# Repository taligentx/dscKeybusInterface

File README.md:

# DSC Keybus Interface

This library directly interfaces Arduino, esp8266, and esp32 series microcontrollers to [DSC PowerSeries](http://www.dsc.com/dsc-security-products/g/PowerSeries/4) and [Classic series](https://www.dsc.com/manual/29000203) security systems for integration with home automation, remote control as a virtual keypad, notifications on alarm events, unlocking installer codes, and emulating DSC panels to use DSC keypads as general purpose input devices.

This enables existing DSC security system installations to retain the features and reliability of a hardwired system while integrating with modern devices and software for under $5USD in components.

The built-in examples can be used as-is or as a base to adapt to other uses:
* Home automation integration: [Home Assistant](https://www.home-assistant.io), [Apple HomeKit & Siri](https://www.apple.com/ios/home/), [Google Home](https://assistant.google.com), [OpenHAB](https://www.openhab.org), [Athom Homey](https://www.athom.com/en/)
* Remote control: Web interface, [Blynk](https://www.blynk.io) mobile app, [Telegram](https://www.telegram.org) bot (with remote arming/disarming via chat)
* Notifications: [Pushover](https://www.pushover.net), [PushBullet](https://www.pushbullet.com), [Pushsafer](https://www.pushsafer.com), [Twilio SMS](https://www.twilio.com), [TinyGSM SMS](https://github.com/vshymanskyy/TinyGSM), E-mail
* Keypad interface: Emulates a DSC panel to connect DSC keypads as physical input devices for any general purpose, without a DSC panel.
* Installer code unlocking: Automatic code search to unlock panels with unknown installer codes

Example integrations:
* [Apple Home & Siri](https://www.apple.com/ios/home/):  
  
* [Home Assistant](https://www.home-assistant.io):  
  
* [OpenHAB](https://www.openhab.org) MQTT:  
  
* [Blynk](https://www.blynk.io) app virtual keypad:
  
* Web virtual keypad:  
  
* [Telegram](https://www.telegram.org) bot:  

## Quick start
1. Install the DSC Keybus Interface library:
    * Arduino IDE: Search for `DSC` in the Library Manager - `Sketch > Include Library > Manage Libraries`  
      
    * PlatformIO IDE: Search for `DSC` in the [PlatformIO Library Registry](https://platformio.org/lib/show/5499/dscKeybusInterface)  
      
    * PlatformIO CLI: `platformio lib install "dscKeybusInterface"`
    * Alternatively, `git clone` or download the repo .zip to the Arduino/PlatformIO library directory to keep track of the latest changes.
2. Select, configure, and upload one of the example sketches to the microcontroller:  
      
3. Connect the microcontroller to the DSC Keybus per the wiring diagram with the appropriate resistors (and a transistor if you'd like to control the system).

## Why?
**I Had**: _A DSC security system not being monitored by a third-party service._  
**I Wanted**: _Notification if the alarm triggered._

I was interested in finding a solution that directly accessed the pair of data lines that DSC uses for their proprietary Keybus protocol to send data between the panel, keypads, and other modules (instead of using the DSC IT-100 serial module).  Tapping into the data lines is an ideal task for a microcontroller and also presented an opportunity to work with the [Arduino](https://www.arduino.cc) and [FreeRTOS](https://www.freertos.org) (via [esp-open-rtos](https://github.com/SuperHouse/esp-open-rtos)) platforms.

While there has been excellent [discussion about the DSC Keybus protocol](https://www.avrfreaks.net/s/topic/a5C3l000000ULgIEAW/t097136) and several existing projects, there were a few issues that remained unsolved:
* Error-prone Keybus data capture.
* Limited data decoding - there was good progress for armed/disarmed states and partial zone status for a single partition, but otherwise most of the data was undecoded (notably missing the alarm triggered state).
* Read-only - unable to control the Keybus to act as a virtual keypad.
* No implementations to do useful work with the data.

This library uses a combination of hardware and timer interrupts to accurately capture Keybus data, and has lead to reverse engineering much of the Keybus protocol.

## Features
* Monitor the status of all partitions:
  - Alarm triggered, armed/disarmed, entry/exit delay, fire triggered, keypad panic keys
* Monitor zones status:
  - Zones open/closed, zones in alarm
* Monitor system status:
  - Ready, trouble, AC power, battery
* Monitor PGM outputs 1-14 status
* Virtual keypad:
  - Write keys to the panel for all partitions
  - Trigger panel command outputs
* Keypad interface:
  - Emulates a DSC panel to use DSC PowerSeries and Classic series keypads as physical input devices for any general purpose, without needing a DSC panel.
* Panel time - retrieve current panel date/time and set a new date/time (including an example with NTP sync)
* Panel installer code unlocking - determine the 4-digit panel installer code
* Virtual zone expander - the [expander branch](https://github.com/taligentx/dscKeybusInterface/tree/expander) can emulate a DSC zone expander module to add zones to the security system that are handled by the microcontroller - thanks to [Dilbert66](https://github.com/Dilbert66) for this contribution!
* Direct Keybus interface:
  - Does not require the [DSC IT-100 serial interface](https://www.dsc.com/alarm-security-products/IT-100%20-%20PowerSeries%20Integration%20Module/22).
* Designed for reliable data decoding and performance:
  - Hardware GPIO pin interrupts and timer interrupts for accurate data capture timing
  - Data buffering: helps prevent lost Keybus data if the sketch is busy
  - Extensive data decoding: the majority of Keybus data as seen in the [DSC IT-100 Data Interface developer's guide](https://cms.dsc.com/download.php?t=1&id=16238) has been reverse engineered and documented in [`src/dscKeybusPrintData.cpp`](https://github.com/taligentx/dscKeybusInterface/blob/master/src/dscKeybusPrintData.cpp).
  - Non-blocking code: Allows sketches to run as quickly as possible without using `delay` or `delayMicroseconds`
* Supported security systems:
  - [DSC PowerSeries](https://www.dsc.com/?n=enduser&o=identify) - all panels are supported, tested with: PC585, PC1555MX, PC1565, PC1565-2P, PC5005, PC5010, PC5015, PC5020, PC1616, PC1808, PC1832, PC1864
  - [DSC Classic series](https://www.dsc.com/?n=enduser&o=identify): PC1500, PC1550, PC2550
    * Requires configuring the panel through `*8` programming to enable PC16-OUT mode - see [DSC Configuration](https://github.com/taligentx/dscKeybusInterface/tree/master?tab=readme-ov-file#dsc-configuration)
    * PC2500 and PC3000 require testing, [post an issue](https://github.com/taligentx/dscKeybusInterface/issues) if you're able to test these panels.
  - Rebranded DSC PowerSeries (such as some ADT systems) should also work with this interface.
* Unsupported security systems:
  - DSC Alexor (PC9155) is all wireless and does not have an accessible Keybus interface.
  - DSC Neo series use a higher speed encrypted data protocol (Corbus) that is not currently possible to support.
  - Other brands (that are not rebranded DSC systems) use different protocols and are not supported.
    * For Honeywell Ademco Vista 15P/20P, see [Dilbert66's esphome-vistaECP](https://github.com/Dilbert66/esphome-vistaECP) project
    * For Paradox systems, see [liaan's paradox-esp8266](https://github.com/liaan/paradox_esp8266) project
* Supported microcontrollers:
    - [Arduino](https://www.arduino.cc/en/Main/Products):
      * Boards: Uno, Mega, Leonardo, Mini, Micro, Nano, Pro, Pro Mini
      * ATmega328P, ATmega2560, and ATmega32U4-based boards at 16Mhz
    - esp8266:
      * Development boards: NodeMCU v2 or v3, Wemos D1 Mini, etc.
      * Includes [Arduino framework support](https://github.com/esp8266/Arduino) and WiFi for ~$3USD shipped.
    - esp32, esp32-s2, esp32-s3, esp32-c3:
      * Includes [Arduino framework support](https://github.com/espressif/arduino-esp32) (v2.0.2 or newer required) for $3-5USD shipped.
* Possible features (PRs welcome!):
  - [DSC IT-100](https://cms.dsc.com/download.php?t=1&id=16238) emulation
  - Unlock 6-digit installer codes

## Release notes
* develop
  - New: Keybus decoding for module programming, PC5200, and zones 33-64 extended status - thanks to [kricon](https://github.com/kricon) for this contribution!
  - New: Classic series PC3000 support (experimental) - with considerations from the PC3000 code by [sfossen](https://github.com/sfossen). The implementations differ, you can also test his original code which is now preserved in the [pc3000 branch](https://github.com/taligentx/dscKeybusInterface/tree/pc3000).
  - New: Isolated `KeybusReader`-specific library functions to capture module data and print Keybus data, reduces size and memory usage across all sketches
  - Updated: `Unlocker` sketch support for DSC Classic series
  - Updated: `HomeAssistant-MQTT` example configuration for Home Assistant core 2022.06, support changing armed modes while armed, add fire/aux/panic buttons
  - Updated: `VirtualKeypad-Web` to support ArduinoJSON 7.x, use LittleFS for esp8266
* 3.0
  - New: DSC Classic series panel support: PC1500, PC1550, PC2550 - thanks to [kricon](https://github.com/kricon) for extensively testing and contributing to this!
  - New: `KeypadInterface` and `KeypadInterface-MQTT` example sketches - emulate a DSC panel to connect DSC PowerSeries and Classic keypads as physical input devices for any general purpose, without needing a DSC panel.
  - New: `HomeKit-HomeSpan` example sketch (esp32) - integrate directly with Apple HomeKit as a native standalone accessory using [HomeSpan](https://github.com/HomeSpan/HomeSpan)
  - New: [Pushover](https://www.pushover.net) and [Pushsafer](https://www.pushsafer.com) push notification example sketches for esp8266/esp32
  - New: esp32-s2 microcontroller support
  - New: Code restructured to support new features from sketches using #define flags - enables Classic series support and `KeypadInterface`.
  - Updated: `Homebridge-MQTT` supports switching armed modes while armed
  - Updated: Added TLS root certificate to `Twilio-SMS`
  - Updated: removed deprecated `handlePanel()`
  - Bugfix: `VirtualKeypad-Web` updated notes to switch to [this fork of ESPAsyncWebServer](https://github.com/arjenhiemstra/ESPAsyncWebServer) to resolve crashes with iOS and macOS clients.
  - Bugfix: `Pushbullet` example sketch updated TLS security certificate fingerprint
  - Bugfix: Workaround for [upstream esp32 TLS handshake issue](https://github.com/espressif/arduino-esp32/issues/6165) preventing making a TLS connection more than once.
  - Bugfix: Fixed `Homebridge-MQTT` handling exit delay states while multiple partitions are arming
  - Bugfix: Resolved access codes not updating on disarm, changed arming access codes to update before armed status changes
* 2.0
  - New: [Telegram](https://www.telegram.org) bot example sketch
  - New: [OpenHAB](https://www.openhab.org) integration example sketch using MQTT
  - New: `Unlocker` example sketch - determines the panel installer code
  - New: `TimeSyncNTP` example sketch - uses NTP to automatically set the panel time
  - New: [ESPHome](https://esphome.io) integration example (located in the `extras` directory) - thanks to [Dilbert66](https://github.com/Dilbert66) for this contribution!
  - New: `TinyGSM-SMS` example sketch - sends status via SMS with a GSM modem - thanks to [jvitkauskas](https://github.com/jvitkauskas) for this contribution!
  - New: `KeybusReaderIP` example sketch enables Keybus data access over IP, thanks to [aboulfad](https://github.com/aboulfad) for this contribution!
  - New: esp32 microcontroller support - requires [Arduino-esp32](https://github.com/espressif/arduino-esp32) v1.0.5-rc6 or newer
  - New: Features for sketches:
      * `ready` and `disabled` track partition status
      * `setTime()` sets the panel date and time
      * `pgmOutputs[]` tracks the status of PGM outputs 1-14
      * `timestampChanged` tracks when the panel sends a timestamp
      * `accessCode` tracks the access code used to arm/disarm
      * `resetStatus()` triggers a full status update of all partitions and zones - for example, after initialization or a lost network connection.
      * `pauseStatus` pauses status updates if set to `true` - for example, holding status changes during a lost network connection
      * `stop()` disables the interface - for example, prior to starting OTA updates
      * `appendPartition()` in example sketches simplifies adding partition numbers to messages
      * `panelVersion` tracks the panel version number
  - New: Handle `*1 bypass/re-activate` used to change stay/away mode while armed
  - Updated: `VirtualKeypad-Blynk` and `VirtualKeypad-Web` display alarm memory, programming zone lights, and event buffer
  - Updated: `HomeAssistant-MQTT, Homebridge-MQTT, OpenHAB-MQTT` include PGM outputs 1-14 status
  - Updated: Virtual keypad writes
      * `write()` for multiple keys can now be set to block until the write is complete with an optional parameter if the char array is ephemeral
      * Checking `writeReady` is typically no longer needed in the sketch, the library will block if a previous write is in progress - this can be checked if the sketch needs to wait until the library can perform a nonblocking write
  - Updated: `HomeAssistant-MQTT` sketch now includes night arm and for esp8266/esp32 includes a sensor with partition status messages
  - Updated: Expanded partition state processing to improve panel state detection at startup
  - Deprecated: `handlePanel()` is now `loop()`
  - Bugfix: Resolved keypad aux/panic key, AC power, and battery status on PC585/PC1555MX
  - Bugfix: Resolved `Homebridge-MQTT` sketch not handling HomeKit target states
  - Bugfix: Resolved timing issues when consecutively calling `write`
* 1.2
  - New: Virtual keypad web interface example, thanks to [Elektrik1](https://github.com/Elektrik1) for this contribution!
    - As of esp8266 Arduino Core 2.5.1, you may need to [manually update the esp8266FS plugin](https://github.com/esp8266/arduino-esp8266fs-plugin) for SPIFFS upload.
  - New: Support esp8266 CPU running at 160MHz - this helps sketches using TLS through BearSSL
  - Updated: HomeAssistant-MQTT example includes availability status, thanks to [bjrolfe](https://github.com/bjrolfe) for this contribution!
  - Updated: List of tested DSC panels: PC585, PC1565, PC5005, PC1808
  - Updated: esp8266 power wiring diagrams
  - Updated: esp8266 module list
* 1.1
  - New: Zones 33-64 tamper and fault decoding
  - New: Push notification example using [Twilio](https://www.twilio.com), thanks to [ColingNG](https://github.com/ColinNg) for this contribution!
  - Bugfix: Zones 17-32 status incorrectly stored
* 1.0
  - New: [Blynk](https://www.blynk.io) virtual keypad example sketch and app layout examples
  - New: Virtual keypad support for PGM terminals 1-4 command output
  - New: Status `keybusConnected` to check if data is being received from the DSC panel
  - New: Auxiliary input alarm decoding
* 0.4
  - New: Virtual keypad support for partitions 3-8, thanks to [jvitkauskas](https://github.com/jvitkauskas) for contributing the necessary logs
  - New: Support ATmega32U4-based Arduino boards (switched to AVR Timer1)
  - Changed: Simplified example names, configurations, added version numbers
  - Bugfix: Virtual keypad writes with partitions 5-8 enabled
  - Bugfix: F/A/P alarm key writes with `processModuleData` disabled
  - Bugfix: HomeAssistant example `configuration.yaml` error for `alarm_control_panel`
* 0.3
  - New: Status for partitions 2-8, zones 33-64
  - New: Virtual keypad support for partition 2
  - New: [Athom Homey](https://www.athom.com/en/) integration example sketch, thanks to [MagnusPer](https://github.com/MagnusPer) for this contribution!
  - New: PCB layouts, contributed by [sjlouw](https://github.com/sj-louw)
  - New: Configurable number of partitions and zones to customize memory usage: `dscPartitions` and `dscZones` in `dscKeybusInterface.h`
  - New: KeybusReader decoding of commands `0xE6` and `0xEB`
  - Changed: Split examples by platform
  - Changed: Arduino sketches no longer use pin 4 to avoid a conflict with the SD card on Ethernet shields.
  - Changed: MQTT examples updated with username and password fields
  - Changed: `processRedundantData` now true by default to prevent storing repetitive data, reduces memory usage.
  - Note: This release changes the library methods to accommodate multiple partitions, existing sketches will need to be updated to match the new example sketches.
* 0.2
  - New: Status for zones 9-32
  - New: [Home Assistant](https://www.home-assistant.io) integration example sketch
  - New: Panel data buffering, adds `dscBufferSize` to `dscKeybusInterface.h` to allow configuration of how many panel commands are buffered to customize memory usage (uses 18 bytes of memory per command buffered).
* 0.1 - Initial release

## Examples
The included examples demonstrate how to use the library and can be used as-is or adapted to integrate with other software.  Post an issue/pull request if you've developed (and would like to share) a sketch/integration that others can use.

* **Status**: Processes and prints the security system status to a serial interface, including reading from serial for the virtual keypad.  This demonstrates how to determine if the security system status has changed, what has changed, and how to take action based on those changes.  Post an issue/pull request if you have a use for additional system states - for now, only a subset of all decoded commands are being tracked for status to limit memory usage:
  * Partitions ready
  * Partitions armed away/stay/disarmed
  * Partitions in alarm
  * Partitions exit delay in progress
  * Partitions entry delay in progress
  * Partitions fire alarm
  * Zones open/closed
  * Zones in alarm
  * PGM outputs 1-14
  * Keypad fire/auxiliary/panic alarm
  * Get/set panel date and time
  * User access code number (1-40)
  * Panel AC power
  * Panel battery
  * Panel trouble
  * Keybus connected

* **HomeKit-HomeSpan** (esp32): Integrates directly with Apple HomeKit as a native accessory (for the Home app and Siri) using [HomeSpan](https://github.com/HomeSpan/HomeSpan), without needing a separate service or device.  Demonstrates arming/disarming partitions, zones status, fire alarms, PGM outputs status, and controlling panel command outputs.
    - For esp8266, the [dscKeybusInterface-RTOS](https://github.com/taligentx/dscKeybusInterface-RTOS) library includes a native HomeKit implementation that runs directly on the esp8266, without requiring a separate device running MQTT or Homebridge.

* **Homebridge-MQTT**: Interfaces with [Homebridge](https://github.com/nfarina/homebridge) via MQTT to integrate with Apple HomeKit (including the iOS Home app and Siri) and [Google Home](https://github.com/oznu/homebridge-gsh).  Demonstrates arming/disarming partitions and for HomeKit, viewing the status of zones, PGM outputs, and fire alarms.

* **HomeAssistant-MQTT**: Interfaces with [Home Assistant](https://www.home-assistant.io) via MQTT.  Demonstrates arming/disarming partitions and viewing the status of zones, PGM outputs, fire alarms, and trouble.  For esp8266/esp32, the partition status is available as a text message for display.

* **OpenHAB-MQTT**: Interfaces with [OpenHAB](https://www.openhab.org) via MQTT.  Demonstrates using the panel and partitions states as OpenHAB switches and zone states as OpenHAB contacts.  For esp8266/esp32, a panel status message is also sent as a string to OpenHAB.  See https://github.com/jimtng/dscalarm-mqtt for an integration using the Homie convention for OpenHAB's Homie MQTT component.

* **ESPHome** (esp8266): Integrates with [ESPHome](https://esphome.io) as a custom component - note that this example is located in the `extras` directory.  Thanks to [Dilbert66](https://github.com/Dilbert66) for this contribution!

* **Homey**: Integrates with [Athom Homey](https://www.athom.com/en/) and the [Homeyduino](https://github.com/athombv/homey-arduino-library/) library, including armed, alarm, and fire states (currently limited to one partition), and zone states.  Thanks to [MagnusPer](https://github.com/MagnusPer) for contributing this example!

* **Telegram** (esp8266/esp32):  Demonstrates sending status updates as push notifications and arming/disarming the security system via a [Telegram](https://www.telegram.org) bot.  Supports iOS, Android, and macOS/Windows/Linux desktop notifications (free).

* **Pushover** (esp8266/esp32):  Demonstrates sending status updates as push notifications via [Pushover](https://www.pushover.net).  Supports iOS, Android, macOS native desktop notifications, and Chrome/Firefox/Safari browser popups ($4.99USD one-time purchase per client platform).

* **Pushbullet** (esp8266/esp32):  Demonstrates sending status updates as push notifications via [Pushbullet](https://www.pushbullet.com).  Supports Android, Windows desktop notifications, and Chrome/Firefox browser popups (free).  Note that iOS is no longer supported.

* **Pushsafer** (esp8266/esp32):  Demonstrates sending status updates as push notifications via [Pushsafer](https://www.pushsafer.com).  Supports iOS, Android, Windows desktop notifications, and Chrome/Firefox/Edge/Opera/Yandex browser popups (€0.99EUR or less per 1000 notifications).

* **Twilio-SMS** (esp8266/esp32): Demonstrates sending status updates as SMS text messages via [Twilio](https://www.twilio.com) - thanks to [ColingNG](https://github.com/ColinNg) for contributing this example!

* **Email** (esp8266/esp32): Demonstrates sending status updates as email.  Email is sent using SMTPS (port 465) with SSL for encryption - this is necessary on the esp8266/esp32 until STARTTLS can be supported.  For example, this will work with Gmail after changing the account settings to [allow less secure apps](https://support.google.com/accounts/answer/6010255).

  This can be used to send SMS text messages if the number's service provider has an [email to SMS gateway](https://en.wikipedia.org/wiki/SMS_gateway#Email_clients) - examples for the US:
  * T-mobile: 5558675309@tmomail.net
  * Verizon: 5558675309@vtext.com
  * AT&T: 5558675309@txt.att.net

* **VirtualKeypad-Blynk** (esp8266/esp32): Provides a virtual keypad interface for the free [Blynk legacy](https://www.blynk.io) app on iOS and Android, including viewing alarm memory, programming zone lights, and the event buffer.  The newer generation Blynk app is not currently supported.  Scan one of the following QR codes from within the Blynk app for an example keypad layout:
  - [Virtual keypad with 16 zones](https://user-images.githubusercontent.com/12835671/103719316-5f6f1d80-4f8e-11eb-8a7c-4bd7bfe3cd8a.png)
  - [Virtual keypad with 32 zones](https://user-images.githubusercontent.com/12835671/103719459-af4de480-4f8e-11eb-8e4a-7172961e2d29.png)
  - [Virtual keypad with 8 zones and event log](https://user-images.githubusercontent.com/12835671/103719518-cc82b300-4f8e-11eb-8b2a-97299e7be3a2.png)

  Note: Installing [Blynk as a local server](https://github.com/Peterkn2001/blynk-server) is recommended to keep control of the security system internal to your network.

* **VirtualKeypad-Web** (esp8266/esp32): Provides a virtual keypad web interface, using the esp8266/esp32 itself as a standalone web server, including viewing alarm memory, programming zone lights, and the event buffer.  Thanks to [Elektrik1](https://github.com/Elektrik1) for contributing this example!

* **TimeSyncNTP**:  Synchronizes and maintains time on PowerSeries panels via an NTP server, including DST adjustments.

* **Unlocker**: Finds the 4-digit installer code for PowerSeries panels by checking all possible codes, including handling keypad lockout if enabled.  The valid code is output to serial as well as repeatedly flashed with the built-in LED.  Arduino checks each code sequentially but esp8266/esp32 may find the code more quickly as they check in order of the [most commonly used general 4-digit codes](http://www.datagenetics.com/blog/september32012).

* **KeypadInterface**:  Interfaces directly to DSC PowerSeries and Classic series (tested with PC1500RK) keypads (without a DSC panel) to enable using these as physical inputs for any general purpose.  Examples included for interfacing via serial and MQTT.  Note that this uses a different wiring setup from the standard Keybus interface, refer to the wiring diagram in the example sketch.

* **KeybusReader**: Decodes and prints data from the Keybus to a serial interface, including reading from serial for the virtual keypad.  This can be used to help decode the Keybus protocol and is also handy as a troubleshooting tool to verify that data is displayed without errors.  For esp8266/esp32, `KeybusReaderIP` enables connectivity over WiFi.

  See [`src/dscKeybusPrintData.cpp`](https://github.com/taligentx/dscKeybusInterface/blob/master/src/dscKeybusPrintData.cpp) for all currently known Keybus protocol commands and messages.  Issues and pull requests with additions/corrections are welcome!

## More DSC projects
* **[dscalarm-mqtt](https://github.com/jimtng/dscalarm-mqtt)**: implementation of the [Homie](https://homieiot.github.io) MQTT convention
* **[esphome-dsckeybus](https://github.com/Dilbert66/esphome-dsckeybus)**: implementation of this library as an ESPHome custom component
* **[PC1500KeybusReader](https://github.com/polishedmarvin/dscKeybusInterface)**: MQTT HomeKit example for the PC1500 and ESP32 using [dougkpowers/pc1550-interface](https://github.com/dougkpowers/pc1550-interface)

## Wiring

```
DSC Aux(+) ---+--- Arduino Vin pin
              |
              +--- 5v voltage regulator --- esp8266 NodeMCU / Wemos D1 Mini 5v pin
                                            esp32 development board 5v pin

DSC Aux(-) --- Arduino/esp8266/esp32 Ground

                        Arduino        +--- dscClockPin (Arduino Uno: 3)
DSC Yellow ---+--- 15k ohm resistor ---|
              |                        +--- 10k ohm resistor --- Ground
              |
              |     esp8266/esp32      +--- dscClockPin (esp8266: D1, GPIO 5 / esp32: 18)
              +--- 33k ohm resistor ---|
                                       +--- 10k ohm resistor --- Ground

                        Arduino        +--- dscReadPin (Arduino Uno: 5)
DSC Green ----+--- 15k ohm resistor ---|
              |                        +--- 10k ohm resistor --- Ground
              |
              |     esp8266/esp32      +--- dscReadPin (esp8266: D2, GPIO 4 / esp32: 19)
              +--- 33k ohm resistor ---|
                                       +--- 10k ohm resistor --- Ground

Classic series only, PGM configured for PC16-OUT mode:
DSC PGM ------+--- 1k ohm resistor --- DSC Aux(+)
              |
              |         Arduino        +--- dscPC16Pin (Arduino Uno: 4)
              +--- 15k ohm resistor ---|
              |                        +--- 10k ohm resistor --- Ground
              |
              |     esp8266/esp32      +--- dscPC16Pin (esp8266: D7, GPIO 13 / esp32: 17)
              +--- 33k ohm resistor ---|
                                       +--- 10k ohm resistor --- Ground

Virtual keypad (optional):
DSC Green ---- NPN collector --\
                                |-- NPN base --- 1k ohm resistor --- dscWritePin (Arduino Uno: 6 / esp8266: D8, GPIO 15 / esp32: 21)
      Ground --- NPN emitter --/
```

* The DSC PowerSeries Keybus operates at ~12.6v and the Classic series operates at ~13.75v, a pair of resistors per data line will bring this down to an appropriate voltage for each microcontroller.
    * Arduino:
      * The DSC yellow (clock) line connects to a [hardware interrupt pin](https://www.arduino.cc/reference/en/language/functions/external-interrupts/attachinterrupt/) - for the Uno, these are pins 2 or 3.  The example sketches use dscClockPin: 3.
      * The DSC green (data) line can be connected to any of the remaining digital pins 2-12.  The examples sketches use dscReadPin: 5 and dscWritePin: 6.
    * esp8266: connect the DSC lines to GPIO pins that are normally low to avoid putting spurious data on the Keybus: D1 (GPIO5), D2 (GPIO4) and D8 (GPIO15).  The example sketches use dscClockPin: D1, dscReadPin: D2, dscWritePin: D8.  For the Classic series, dscPC16Pin: D7 (GPIO 13).
    * esp32: connect the DSC lines to GPIO pins that do not send signals at boot: 4, 13, 16-39.  For virtual keypad, use pins 4, 13, 16-33 - pins 34-39 are input only and cannot be used.  The example sketches use dscClockPin: 18, dscReadPin: 19, dscWritePin: 21.  For the Classic series, dscPC16Pin: 17.
* Virtual keypad uses an NPN transistor and a resistor to write to the Keybus.  Most small signal NPN transistors should be suitable, for example:
  * 2N3904
  * BC547, BC548, BC549
  * That random NPN at the bottom of your parts bin (my choice)
* Power:
  * Arduino boards can be powered directly from the DSC panel
  * esp8266/esp32 development boards should use an external voltage regulator set to 5v to the 5v pin:
    - LM2596-based step-down buck converter modules are reasonably efficient and commonly available for under $1USD shipped (eBay, Aliexpress, etc) - these are the modules I use.
    - MP2307-based step-down buck converter modules (aka Mini360) are also available but some versions run hot with an efficiency nearly as poor as linear regulators.
    - Linear voltage regulators (LM7805, etc) will work but are inefficient and run hot - these may need a heatsink.
  * esp8266/esp32 boards can also use an external voltage regulator set to 3.3v to the 3.3v pin - this bypasses the module's onboard voltage regulator.  For example, some Wemos D1 mini clones use [low current voltage regulators](https://www.letscontrolit.com/forum/viewtopic.php?t=6603) that can cause stability issues.  NodeMCU boards are not affected as they use the more powerful AMS1117 regulator.
* Connections should be soldered, breadboards can cause issues.

## Virtual keypad
This allows a sketch to send keys to the DSC panel to emulate the physical DSC keypads and enables full control of the panel from the sketch or other software.

Keys are sent to partition 1 by default and can be changed to a different partition.  The following keys can be sent to the panel - see the examples for usage:

* Keypad: `0-9 * #`
* Arm stay (requires access code if quick arm is disabled): `s`
* Arm away (requires access code if quick arm is disabled): `w`
* Arm with no entry delay (requires access code): `n`
* Fire alarm: `f`
* Auxiliary alarm: `a`
* Panic alarm: `p`
* Door chime enable/disable: `c`
* Fire reset: `r`
* Quick exit: `x`
* Change partition: `/` + `partition number` or set `writePartition` to the partition number.  Examples:
  * Switch to partition 2 and send keys: `/2` + `1234`
  * Switch back to partition 1: `/1`
  * Set directly in sketch: `dsc.writePartition = 8;`
* Command output 1: `[`
* Command output 2: `]`
* Command output 3: `{`
* Command output 4: `}`

## DSC Configuration
Panel options affecting this interface, configured by `*8 + installer code` - see the `Unlocker` sketch if your panel's installer code is unknown.  Refer to the DSC installation manual for your panel to configure these options:
* Swinger shutdown: By default, the panel will limit the number of alarm commands sent in a single armed cycle to 3 - for example, a zone alarm being triggered multiple times will stop reporting after 3 alerts.  This is to avoid sending alerts repeatedly to a third-party monitoring service, and also affects this interface.  As I do not use a monitoring service, I disable swinger shutdown by setting this to `000`.
  - PC1555MX/5015: section `370`
  - PC1616/PC1832/PC1864 section `377`
  - PC1500/PC1550: section `15`
  - PC2550: section `22`

* AC power failure reporting delay: The default delay is 30 minutes and can be set to `000` to immediately report a power failure.
  - PC1555MX/5015: section `370`
  - PC1616/PC1832/PC1864 section `377`
  - PC1500/PC1550: section `17`
  - PC2500: section `16`
  - PC2550: section `20`
  - PC3000: section `22`

* Classic series - requires PC16-OUT mode to get the security system status (see wiring section):
  - Communicator: Enable to support PC16-OUT mode (if not using a monitoring service, "Communicator Call Directions" options can be set to `0`)
    - PC1500/PC1550: section `12`, option `1` off
    - PC2500: section `13`, option `1` off
    - PC2550: section `15`, option `1` off
    - PC3000: section `18`, option `1` off
  - PC16-OUT: Enable to set the PGM output to PC16-OUT mode to send required panel status data on the Keybus.
    - PC1500/PC1550: section `13`, option `4` on
    - PC2500: section `14`, option `4` on
    - PC2550: section `16`, option `4` on
    - PC3000: section `19`, option `4` on
  - PGM output: Set to "Strobe output" mode to track when the alarm is tripped.
    - PC1500/PC1550: section `24`, option `08`
    - PC2500: section `22`, option `x8` (first digit is aux input zone configuration, default `2`)
    - PC2550: section `30`, option `x8`
    - PC3000: section `28`, option `x8`

## Notes
* For OTA updates on esp8266 and esp32, you may need to stop the interface using `dsc.stop();`:
  ```
  void setup() {
    ...
    ArduinoOTA.onStart( {
      dsc.stop();
    ...
  ```
* Memory usage can be adjusted based on the number of partitions, zones, and data buffer size specified in [`src/dscKeybus.h`](https://github.com/taligentx/dscKeybusInterface/blob/master/src/dscKeybus.h) or [`src/dscClassic.h`](https://github.com/taligentx/dscKeybusInterface/blob/master/src/dscClassic.h).   Default settings:
  * Arduino: up to 4 partitions, 32 zones, 10 buffered commands
  * esp8266/esp32: up to 8 partitions, 64 zones, 50 buffered commands

* PCB layouts are available in [`extras/PCB Layouts`](https://github.com/taligentx/dscKeybusInterface/tree/master/extras/PCB%20Layouts) - thanks to [sjlouw](https://github.com/sj-louw) for contributing these designs!

* Support for other platforms depends on adjusting the code to use their platform-specific timers.  In addition to hardware pin-change interrupts to capture the DSC clock, this library uses platform-specific timer interrupts to capture the DSC data line in a non-blocking way 250μs after the clock changes (without using `delayMicroseconds()`).  This is necessary because the clock and data are asynchronous - I've observed keypad data delayed up to 160μs after the clock falls.

* Resource utilization:
  * Arduino: 1 hardware interrupt digital pin, 2 digital pins (+1 for Classic series), Timer1 interrupt
  * esp8266: 3 digital pins (+1 for Classic series), timer1 interrupt
  * esp32 series: 3 digital pins (+1 for Classic series), timer0 interrupt

## Troubleshooting
If you are running into issues:
1. Run the `KeybusReader` example sketch and view the serial output to verify that the interface is capturing data successfully without reporting checksum errors.
    * If data is not showing up or has errors, check the clock and data line wiring, resistors, and all connections.  Breadboards can cause issues, connections should be soldered instead.
    * Power supply issues can also cause data errors or microcontroller crashes/reboots - if this occurs, test with an external power supply set to 5v (Arduino) or 3.3v (esp8266/esp32) and connected to the matching voltage pin (bypassing the voltage regulator on development boards).
2. For virtual keypad, run the `KeybusReader` example sketch and enter keys through serial and verify that the keys appear in the output and that the panel responds.
    * If keys are not displayed in the output, verify the transistor pinout, base resistor, and wiring connections.
3. Run the `Status` example sketch and view the serial output to verify that the interface displays events from the security system correctly as partitions are armed, zones opened, etc.

For general discussions, feature requests, or how-to issues, you can [post in Discussions](https://github.com/taligentx/dscKeybusInterface/discussions), or [post an Issue](https://github.com/taligentx/dscKeybusInterface/issues) if it looks like an issue with the library code itself.

## References
[AVR Freaks - DSC Keybus Protocol](https://www.avrfreaks.net/s/topic/a5C3l000000ULgIEAW/t097136): An excellent discussion on how data is sent on the Keybus.

[stagf15/DSC_Panel](https://github.com/stagf15/DSC_Panel): A library that nearly works for the PC1555MX but had timing and data errors.  Writing this library from scratch was primarily a programming exercise, otherwise it should be possible to patch the DSC_Panel library.

[dougkpowers/pc1550-interface](https://github.com/dougkpowers/pc1550-interface): An interface for the DSC Classic series.

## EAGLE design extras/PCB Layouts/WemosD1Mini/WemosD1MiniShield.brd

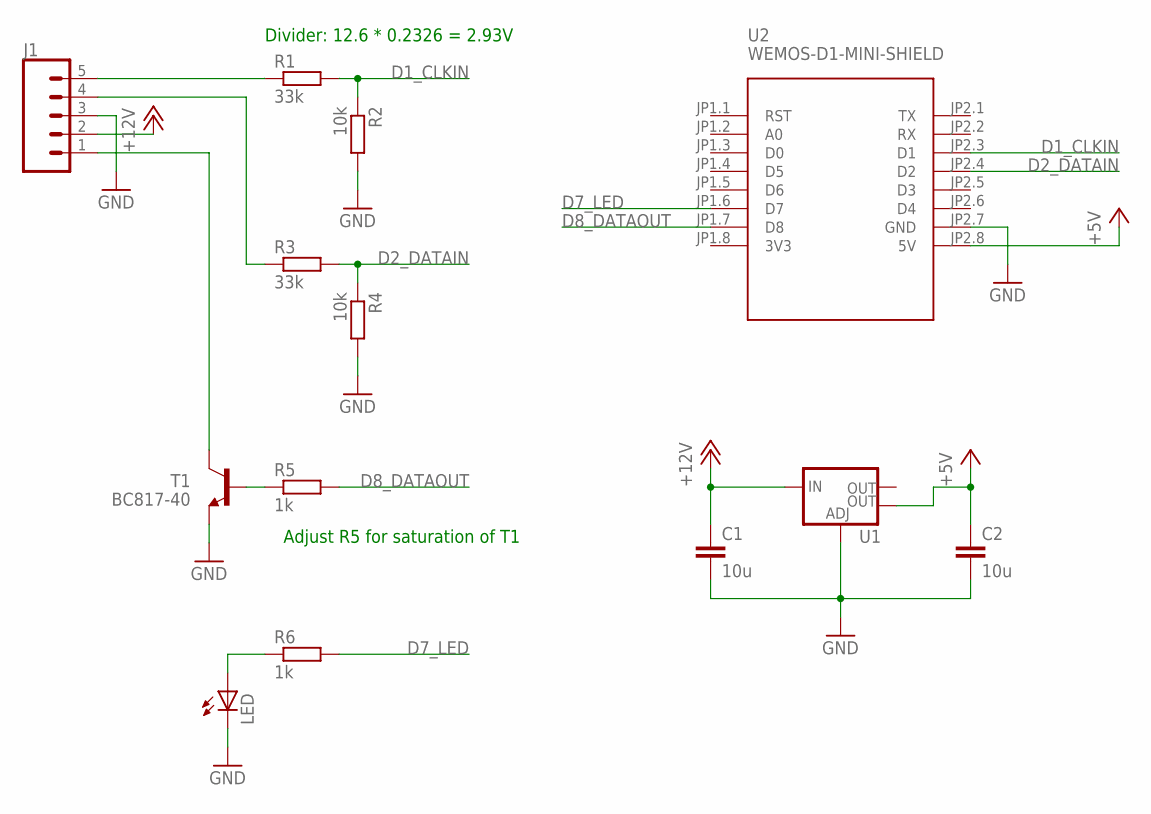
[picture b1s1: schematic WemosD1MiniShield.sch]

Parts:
C1, C2: 10u; C0805
J1: CONN_05LOCK; 1X05_LOCK
LED: LED1206; LED-1206
R1, R3: 33k; R0805
R2, R4: 10k; R0805
R5, R6: 1k; R0805
T1: BC817-40; SOT23-BEC
U1: V_REG_LM1117SOT223; SOT223
U2: WEMOS-D1-MINI-SHIELD

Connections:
3V3: U2.JP1.8 (3V3)
+5V: C2.1, U1.4 (OUT), U2.JP2.8 (5V)
+12V: C1.1, J1.2, U1.3 (IN)
D1_CLKIN: R1.2, R2.1, U2.JP2.3 (D1)
D2_DATAIN: R3.2, R4.1, U2.JP2.4 (D2)
D7_LED: R6.2, U2.JP1.6 (D7)
D8_DATAOUT: R5.2, U2.JP1.7 (D8)
GND: C1.2, C2.2, J1.3, LED.C, R2.2, R4.2, T1.E, U1.1 (ADJ), U2.JP2.7 (GND)
unnamed: J1.5, R1.1
unnamed: J1.4, R3.1
unnamed: J1.1, T1.C
unnamed: R5.1, T1.B
unnamed: LED.A, R6.1

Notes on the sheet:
Divider: 12.6 * 0.2326 = 2.93V
Adjust R5 for saturation of T1

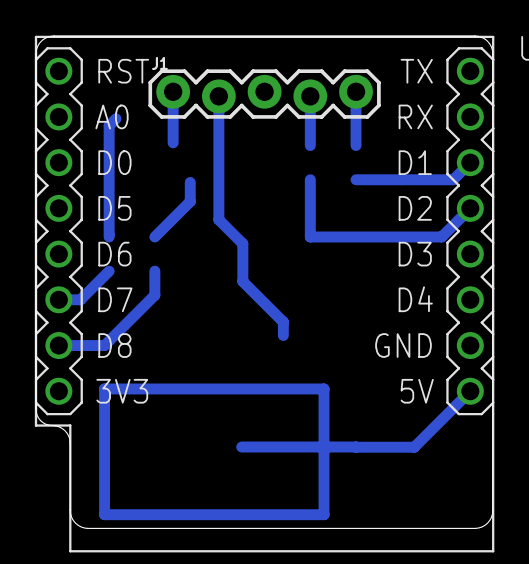
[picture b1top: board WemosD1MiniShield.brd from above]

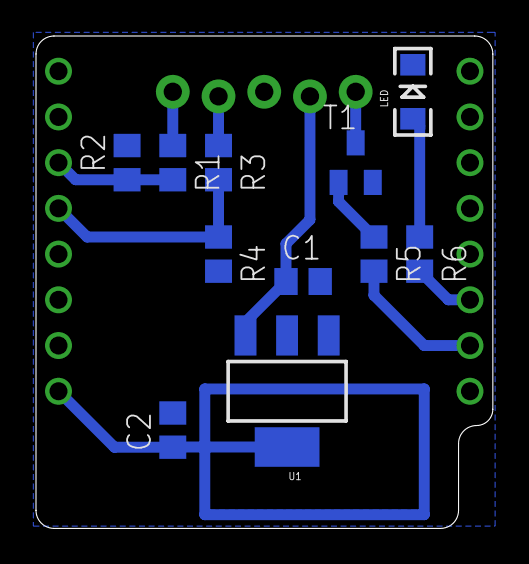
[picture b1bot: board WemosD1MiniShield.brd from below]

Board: 2 copper layers, 25.4 x 27.4 mm, 13 parts (11 on the bottom side), 12 nets.

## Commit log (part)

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2018-05-04 Add option hideKeypadDigits for public logs
2018-05-06 Add zones 9-32, update Status examples to check all zones
2018-05-09 Fix regression for processing arming without entry delay and activating stay/away zones
2018-05-14 Add panel data buffer, update examples
2018-05-15 Add Platform.io config, update version, add fire and alarm key status to examples
2018-05-18 Add newly decoded status, update examples documentation
2018-05-20 Update DSC configuration information for multiple panels
2018-05-22 Refactor command 0xA5 decoding (#9, #10), add Homey (#13) and virtual keypad (#14) documentation, remove dscTime
2018-05-28 Implement multiple partitions support
2018-05-31 Update 0x0A partition decoding
2018-06-01 Update to support access code entry with quick arm disabled.
    As per commit ac6e070a1c06880e9cb153b3a06e6f675d8dbfbe.
2018-06-05 Implement multiple partitions
2018-06-07 Simplify public method names
2018-06-07 Note availability of develop branch
2018-06-10 Rename keypad data to module data
2018-06-11 Add additional full PCB schematic
2018-06-12 Update Arduino Homeassistant sketch to support multiple partitions
2018-06-14 Update for 0.3 release
2018-06-18 Add virtual keypad partitions 5-8
2018-06-24 Fix F/A/P alarm with module data disabled
2018-07-05 Add virtual keypad PGM 1-4 command output
2018-07-07 Update README.md, examples
2018-07-17 Add zones 33-64 tamper and fault decoding
2018-08-02 Added example for Twilio
2018-09-01 Screenshots added
2018-09-03 Created DSC font for icons
2018-12-15 OTA Updates
    I've modified this code to accept OTA (over the air) updates. It might need a bit more tweaking and this could be applied to all the other examples too. Also moved Wifi setup into it's own function
2019-05-21 Release 1.2
2019-05-24 Add ability to update status on demand #42
2019-06-04 Set dsc.year to 4 digits, rename timeAvailable to timestampChanged
2019-06-06 Add Arduino HASS sketch keybus status check, doc cleanup
2019-06-06 Update dsc.setTime() parameters order
2019-06-13 Relabel getStatus() to resetStatus()
2019-06-14 initial version for KeybusReaderIP.ino
2019-06-14 nb paritition/zone change
2019-06-15 added KeybusReaderIP.ino
2019-06-15 silly change so PR has .ino ONLY
2019-06-17 Minor bufferOverflow update, fix Homebridge target states #92
2019-06-20 Fixed misplaced }
2019-06-25 Fix lame bug
2019-06-28 Add redundancy for alarm disarmed status #100
2019-07-12 Add OpenHAB example sketches (#107)
2019-07-16 Add Unlocker example sketch (#101)
2019-07-18 Unlocker - implement pause/resume, esp8266 code checking by frequency (#101)
2019-07-20 Update beep, tone, buzzer command decoding
2019-07-22 Resolved keypad aux/panic key, AC power, and battery status on PC585/PC1555MX #108
2019-07-25 Implement partition disabled status checking
2019-07-28 Update partition state processing, change setTime() to bool to catch invalid times
2020-07-24 Remove default to esphome master password on disarm. Force code send. Force code send for night arm
2020-07-25 switched to std::string for code parameter
2020-07-26 Add check for numeric code
2020-07-26 Switch to using subm
2020-07-28 fixed invalid comment
2020-08-07 - add ESPHOME example
2020-08-11 comment case default: return; to process 0xA5 in processPanelStatus0
2020-09-20 try to decode datetime 0xAA command
2020-09-21 add index decode
2020-09-21 modify display
2020-09-27 translate
2020-09-29 change decoding mode
2020-10-01 Update esp8266 wiring resistors in examples, remove exit delay status from OpenHAB examples #107
2020-10-05 Add zone expanders 1-6 responses
2020-10-05 - merged zone expander and relay module changes
2020-10-06 - adjusted code for older version pc5010 with smaller 05/11 cmds
2020-10-07 - fixed wrong channel in addrelay (missed it last commit)
2020-10-08 - fixed dumb mistake in addrequesttoqueue
2020-10-15 Decode zone expander slots 9-11 #64, wireless module battery states #162
2020-10-20 Add zone module slot 8 decoding, fix 0xEB zone tamper decoding #162
2020-10-20 Update 0x16 decoding with panel version, *8 programming #166
2020-11-02 Update 0xE6-0x1A decoding #162
2020-11-12 Reduce KeybusReader flash usage for Arduino AVR
2020-11-22 - ISR and IRAM useage optimizations
2020-11-25 - reset test flag
2020-11-26 - added checkto prevent processing module commands when waiting for asterisk response
2020-11-26 KeybusReader: consolidate 0xAA event buffer code #155
2020-11-30 KeybusReader: fix PC5208 supervisory #64, module tamper #166, keys in programming #174, decode event buffer 0xEC #175 #155, 0x87 PGM 5-14 #64, 0xE6.1F buzzer
2020-12-01 Add gerber files for Wemos D1 Mini shield
2020-12-02 KeybusReader - update disabled partitions #64
2020-12-02 Add ESPHome example to extras directory
2020-12-06 KeybusReader: add 0x57 wireless keys #175, zone expander 1-6 status, add *1,*2,*3 user codes, fix zone expander 4-7 decoding
2020-12-09 Added printPanelStatus 0x05, 0x18. Seperated 0x14, 0x17 and 0x1B.
    0x14/0x17/0x1B data was overlapping, so it needed to be seperated
    0x05: arm/disarm user 35-39, 43-95
    0x14: Tlink module data
    0x17: *1/*2/*3 access user 35-39, 43-95
    0x18: *5/*6/user code access 35-39, 43-95
    0x1B: System reset transmission
2020-12-10 Added support for access codes 35-95 arm/disarm, *1, *2, *3, *5, *6, *7, *9
    printPanelAccessCode needs a version check to correctly show user code prefix (users 33, 34, 41, 42)
    Panels with version 4.2 and above have more user codes and each can be set as supervisor/durres
    Tested random codes in range 1-75, works nice on PC1832. 75-95 pending testing but range matches fine.
2020-12-11 Renamed accessIncrease to accessCodeIncrease for better readability
2020-12-11 Addition to 0xC3 cmd dialer call attempt and call attempts ended
2020-12-12 Added more keypad function keys, event buffer treshold
    Renamed "PGM2 input trouble/restore" to "Fire zone trouble/restore" to match event buffer naming scheme.
2020-12-13 Added few new status messages to VirtualKeypad-Web
2020-12-17 Add PGM 1-14 status #166, update MQTT examples with PGM status, consolidate status processing code
2020-12-23 Update Status examples to simplify access codes #181
2020-12-23 KeybusReader: additional keypad keys commands
2020-12-26 Fixed few typos
2020-12-27 Added Downloading in progress and Wireless notification msgs
    Downloading in progress message is displayed on all LCD keypads while panel is connected on DLS.
    When 0xB1 byte5 bit1 is zero seems to be related to Wireless notifications, it can be for status/troubles of wireless zones?
2020-12-29 Consolidated *7 command output 0xB2 & 0xB3 msg, fix switch hex order typo
2021-01-01 VirtualKeypad-Blynk: handle displaying zone lights in alarm memory/programming, update partition disabled status handling
2021-01-01 Fix * key handling in programming modes
2021-01-04 Workaround for esp32 core timer bug, add esp32 VirtualKeypad-Web sketch, update esp32 VirtualKeypad-Blynk with zone lights in alarm memory/programming
2021-01-04 Add VirtualKeypad-Web placeholder for event buffer info
2021-01-05 Add panic button example to HomeAssistant #83
2021-01-05 Added *2 Sensors with RF Delinquency
    To VirtualKeypad Blynk and Web examples, viewable by *2 -> 7 -> 7 -> 7 -> 7.
2021-01-06 Update Blynk data display spacing
2021-01-07 Add SMS example for esp32
2021-01-09 Added missing partition messages to HomeAssistant-MQTT examples
    ...to match the ones in dscKeybusPrintData.cpp and VirtualKeypad examples (except 0xC7 msg).
    Possibly, the same needs to be done onto OpenHAB-MQTT examples as well.
2021-01-11 Added printPanelMessages() 0x17 - still fits into Arduino Uno
2021-01-12 Distinguish when keypad accepts HEX-input or just numerical digits
2021-01-13 Blynk boolean for LCD output, 0xC3 unknown data, Reduced flash usage
    Added boolean to disable LCD display data printout in Blynk examples
    Removed calling printUnknownData function from switch statemets - reduces flash size.
    Moved some often used messages from PROGMEM into SRAM (most of it was already in SRAM so its usage is pretty much still the same).
    Renamed Auxiliary input alarm into PGM2 input alarm as it is more understandable and on every panel it can be only used as a PGM2 input.
    Added printModule_0x94, added some info on printPanel_0x8D/0x94
    printPanel_0xC3 checks for unknown data on Byte2 (should work now)
2021-01-22 Rename TinyGSM-SMS example
2021-01-24 Update Classic series wiring diagram
2021-01-31 Blynk fix for partitions 2-8, Push notifications for power/battery/alarm
    Blynk examples now call pauseZones on partitions other than 1 #190
    Memory/Programming leds now also work on partition 2, doesn't work for partitions 3-8 for reason taligentx stated in #182
    Viewing event buffer now also works fine on partitions 2-8.
    Added push notification for battery/power trouble/restore and partition in alarm (partition you've selected in blynk project). Note that you must add widget:notification in your blynk project and ena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
2021-01-31 Added Blynk push notifications for troubles and other partitions in alarm
    If power/battery trouble/restore occur, it will be pushed as notification and "Trouble status on" notification wont be pushed.
    Obviously, if power/battery trouble is active and new trouble occurs such as zone sensor low battery, "Trouble status on" won't be pushed as trouble status was already on.
2021-02-04 Update Classic series configuration notes
2021-02-09 KeypadInterface - add Classic series keypad support (PC1500RK) #200
2021-02-15 TinyGSM-SMS Arduino example, KeypadInterface send LCD Messages
2021-03-24 Create examples_esp8266.yml
    Added auto-compilation of ESP8266 examples
2021-05-21 Update classic series decoding for PC2550 #196
2021-05-22 Updated PC2550 classic series for KeypadInterface example
    Verified with Wemos D1 and PC2550RK keypad using KeypadInterface example
    Keypad beeps and flashing lights aren't yet supported on Classic keypad series
    PC2550 (and PC3000) can't distinguish Zone alarms on zones 5-8 and 9-16
2021-05-26 Update Telegram.ino
    Updated commend on user & and token. Changed structure so it would build in platformio.
2021-05-28 Revert "Update Telegram.ino"
    This reverts commit cfcbd770
2021-06-02 Fixed typo in ESP8266 HomeAssistant-MQTT example
2021-12-23 Update Pushbullet example HTTPS root certificate #259
2022-01-27 Fix esp32 Email example sketch messages
2022-02-01 Add Pushover example sketch for esp8266/esp32
2022-02-10 Fix access code entry on lower number partitions while higher number partitions are in exit delay #272
2022-02-11 Reverted module programming messages (with additional info for ESP)
2022-02-24 Add HomeKit-HomeSpan example sketch
2022-03-15 Fix handling disarm access code #284
2022-03-18 Release 3.0
2022-04-25 - added missing file
2022-06-16 Very Large commit, sorry :) TLDR: - fix multi-char writer - refactor to reduce repeated code - refactor print functions - refactor interrupt handlers - reversed the bit order in interrupt to make dat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
2022-06-18 fix compiler warnings on higher settings
2022-06-28 PC5200 1-4 AUX PTC protection trouble/restore
    Decoded by https://github.com/Alviunta in https://github.com/taligentx/dscKeybusInterface/issues/295
2022-07-01 Fit code into new KeybusReader isolated structure
    Sketch fits into Arduino Uno memory size - using 31422 bytes
2022-08-31 Typo
2023-11-16 Adding missing default values during init. Some of the "changed" variables were not re-initialized properly causing invalid states.

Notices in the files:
parts and their libraries:
SparkFun-Connectors: Licensing: Creative Commons ShareAlike 4.0 International - https://creativecommons.org/licenses/by-sa/4.0
diy-modules: Released under the Creative Commons Attribution 4.0 International License: http://creativecommons.org/licenses/by/4.0
